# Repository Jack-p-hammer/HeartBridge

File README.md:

# HeartBridge

Software, electronics, mechanical parts and simulation for HeartBridge, an automated CPR machine. The project started as MIT 2.009 Green Team's 2025 class project and has continued since.

## Repository layout

| Folder | Contents |
|---|---|
| [`Raspberry Pi code/`](Raspberry%20Pi%20code/) | The Python controller that runs on the Raspberry Pi: state machine, sensing, motor control (moteus), screen and audio prompts, tests and bench scripts. See its [README](Raspberry%20Pi%20code/README.md) for setup. |
| `hardware/pcb/main-board/` | KiCad project for the main CPR machine board, plus its fab outputs in `production/` |
| `hardware/pcb/mcu-board/` | KiCad project for the MCU board |
| `hardware/pcb/contactor-board/` | KiCad project for the contactor board |
| `hardware/pcb/single-pager-legacy/` | Earlier single-sheet version of main board, kept for reference |
| `hardware/mechanical/` | 3D-print sources (`.step`, `.3mf`) for the current HeartBridge iteration |
| `simulation/` | Simulink model (`Heartbridge.slx`) and supporting MATLAB scripts. `legacy-m4/` holds the force sensor calibration from the class project. |
| `docs/` | Project documentation |

## Getting started

- **Controller code:** follow [`Raspberry Pi code/README.md`](Raspberry%20Pi%20code/README.md).
- **PCBs:** open the `.kicad_pro` file in a board's folder with KiCad. Custom symbol and footprint libraries live inside each board folder and are referenced relative to it.
- **Simulation:** in MATLAB, run `simulinkSetup.m` then open `Heartbridge.slx`.

## History

The repository was reorganized out of its class-project layout (`M3`–`M6`, `CPR Machine`, etc.) in October 2026. Older work is kept in tags rather than folders:

- `pre-restructure`: the last commit before the reorganization
- `archive/final`, `archive/integration`, `archive/zeroing`, `archive/hmi_v2`: class-era branches

To look at one, run `git checkout <tag>`. To keep working from one, create a branch: `git switch -c <name> <tag>`.

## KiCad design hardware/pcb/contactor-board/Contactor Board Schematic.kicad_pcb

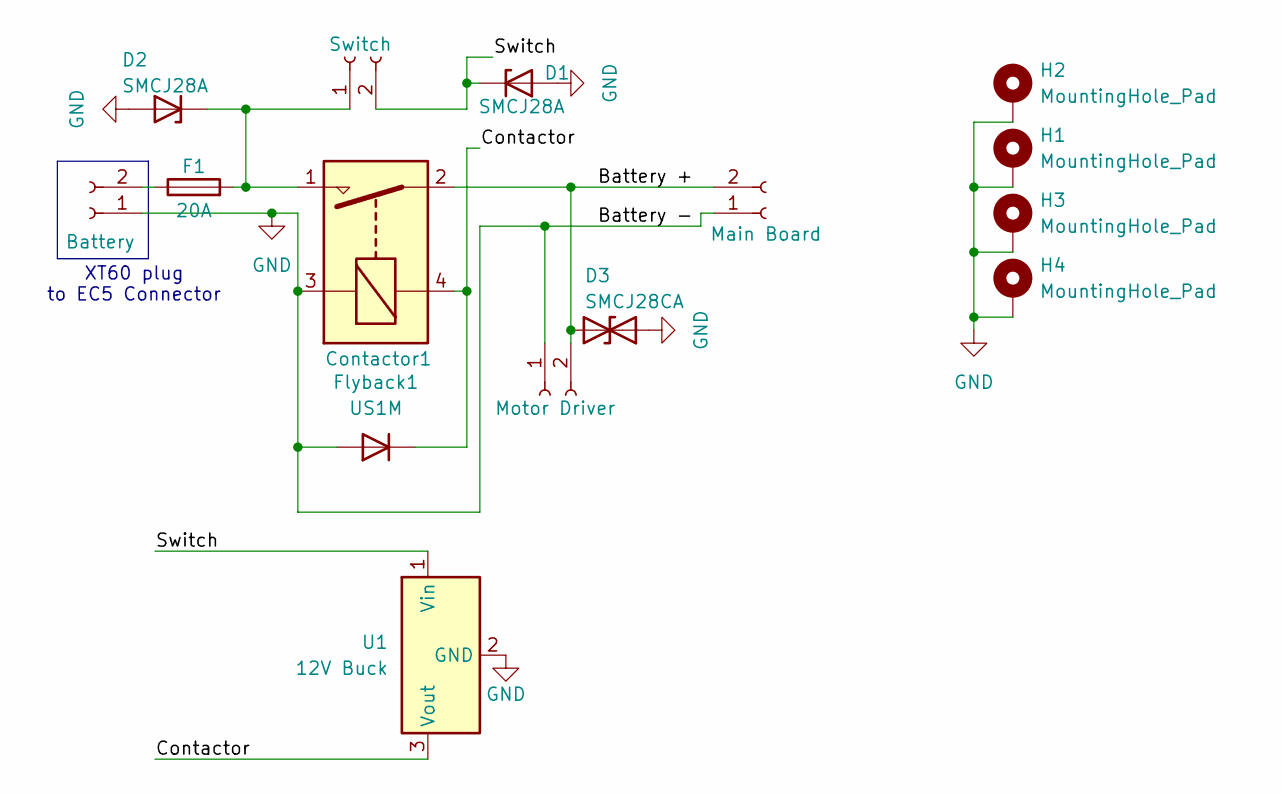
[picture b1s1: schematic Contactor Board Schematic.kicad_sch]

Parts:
Contactor1: AEV20E-BP; AEV20EBP; digikey 2040-AEV20E-BP-ND
D1, D2: SMCJ28A; D_SMC; digikey SMCJ28ALFCT-ND
D3: SMCJ28CA; D_SMC; digikey SMCJ28CALFCT-ND
F1: 20A; Fuse_1206_3216Metric; digikey 5923-0685H9200-01CT-ND
Flyback1: US1M; D_SMA; digikey 4878-US1MCT-ND
H1, H2, H3, H4: MountingHole_Pad; MountingHole_2.7mm_Pad
J_EXT1: Main Board; AMASS_XT30U-M_1x02_P5.0mm_Vertical
J_EXT2: Battery; AMASS_XT60-M_1x02_P7.20mm_Vertical
J_EXT3: Motor Driver; AMASS_XT30U-M_1x02_P5.0mm_Vertical
J_EXT4: Switch; AMASS_XT30U-M_1x02_P5.0mm_Vertical
U1: 12V Buck; Converter_DCDC_TRACO_TSR-1_THT; digikey 1951-2739-ND

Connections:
/Battery +: Contactor1.2, D3.2 (A2), J_EXT1.2, J_EXT3.2
/Contactor: Contactor1.4, Flyback1.1 (K), U1.3 (Vout)
/Switch: D1.1 (K), J_EXT4.2, U1.1 (Vin)
GND: Contactor1.3, D1.2 (A), D2.2 (A), D3.1 (A1), Flyback1.2 (A), H1.1 (1_1), H2.1 (1_1), H3.1 (1_1), H4.1 (1_1), J_EXT1.1, J_EXT2.1, J_EXT3.1, U1.2 (GND)
unnamed: Contactor1.1, D2.1 (K), F1.2, J_EXT4.1
unnamed: F1.1, J_EXT2.2

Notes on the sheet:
XT60 plug to EC5 Connector

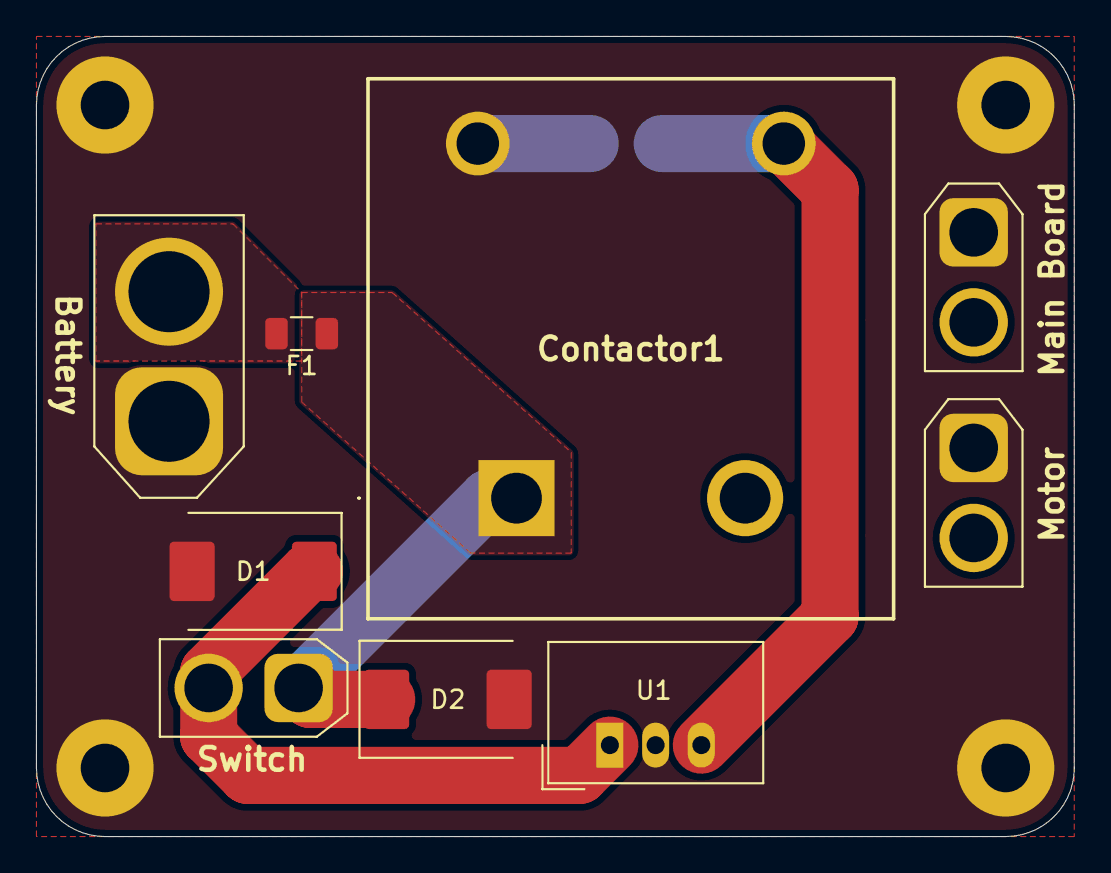
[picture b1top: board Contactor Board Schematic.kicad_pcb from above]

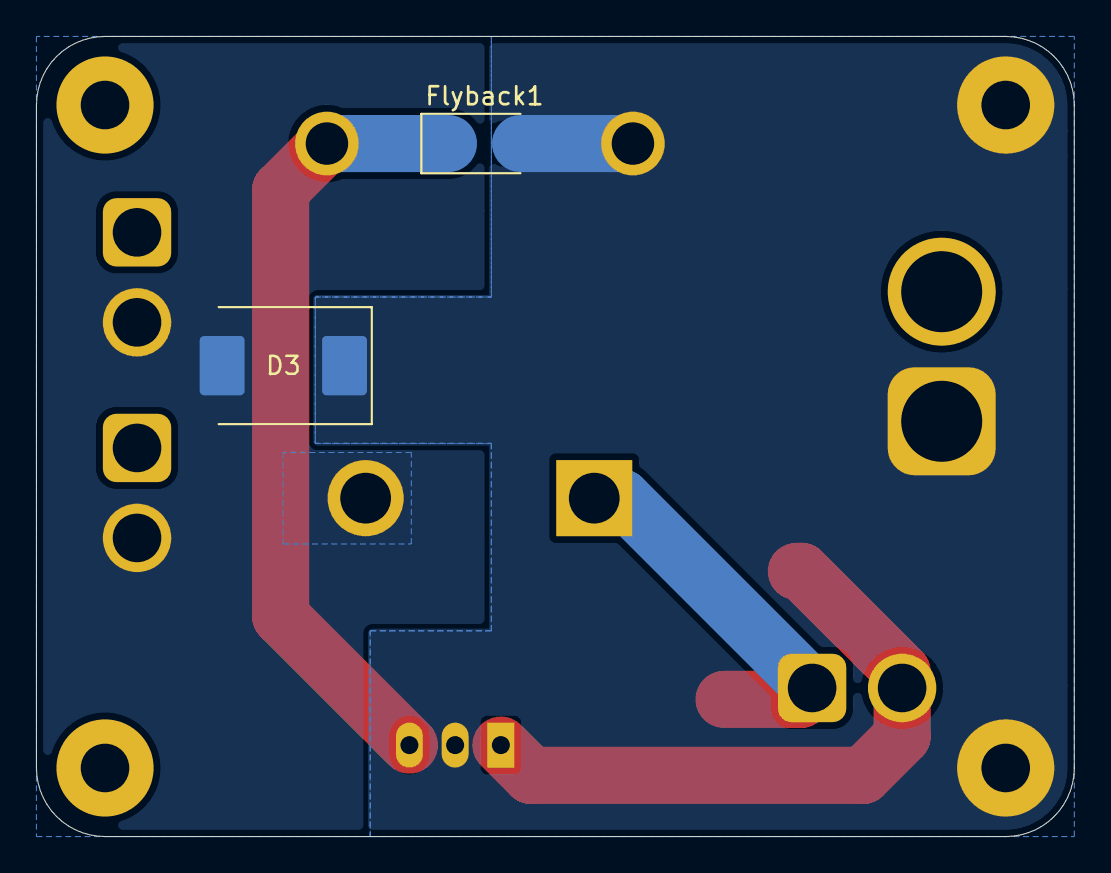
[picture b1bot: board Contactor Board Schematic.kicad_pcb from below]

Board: 2 copper layers, 57.7 x 44.5 mm, 15 parts (2 on the bottom side), 6 nets.

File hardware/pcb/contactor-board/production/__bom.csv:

Designator,Footprint,Quantity,Value,LCSC Part #
CONTACTOR1,AEV20EBP,1,AEV20E-BP,
"D1, D2",D_SMC,2,SMCJ28A,
D3,D_SMC,1,SMCJ28CA,
F1,1206,1,20A,
FLYBACK1,D_SMA,1,US1M,
J_EXT1,AMASS_XT30U-M_1x02_P5.0mm_Vertical,1,Main Board,
J_EXT2,AMASS_XT60-M_1x02_P7.20mm_Vertical,1,Battery,
J_EXT3,AMASS_XT30U-M_1x02_P5.0mm_Vertical,1,Motor Driver,
J_EXT4,AMASS_XT30U-M_1x02_P5.0mm_Vertical,1,Switch,
U1,Converter_DCDC_TRACO_TSR-1_THT,1,12V Buck,

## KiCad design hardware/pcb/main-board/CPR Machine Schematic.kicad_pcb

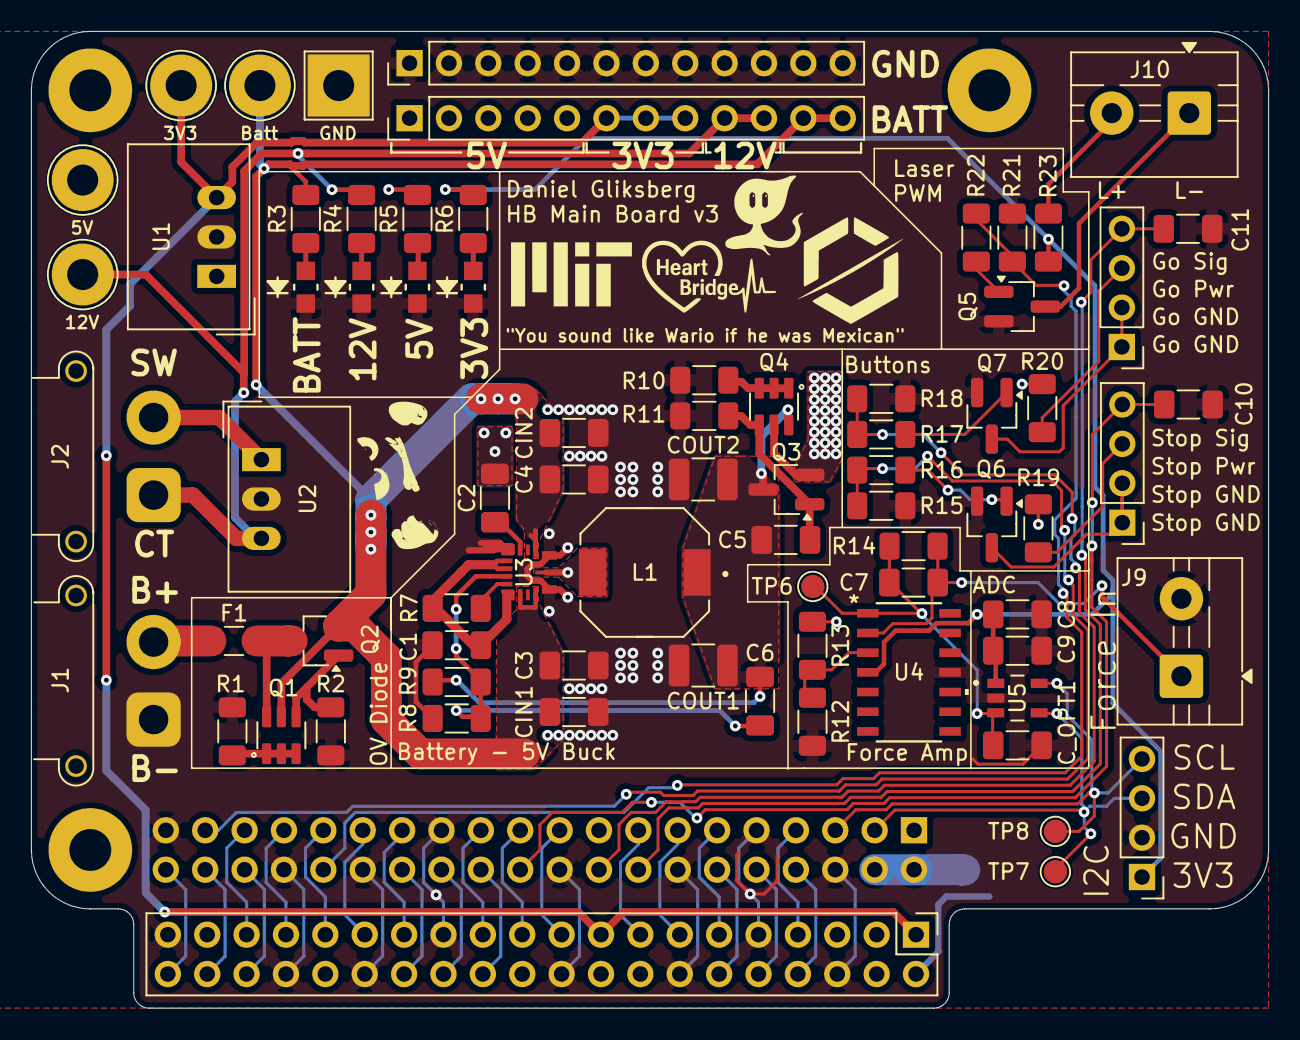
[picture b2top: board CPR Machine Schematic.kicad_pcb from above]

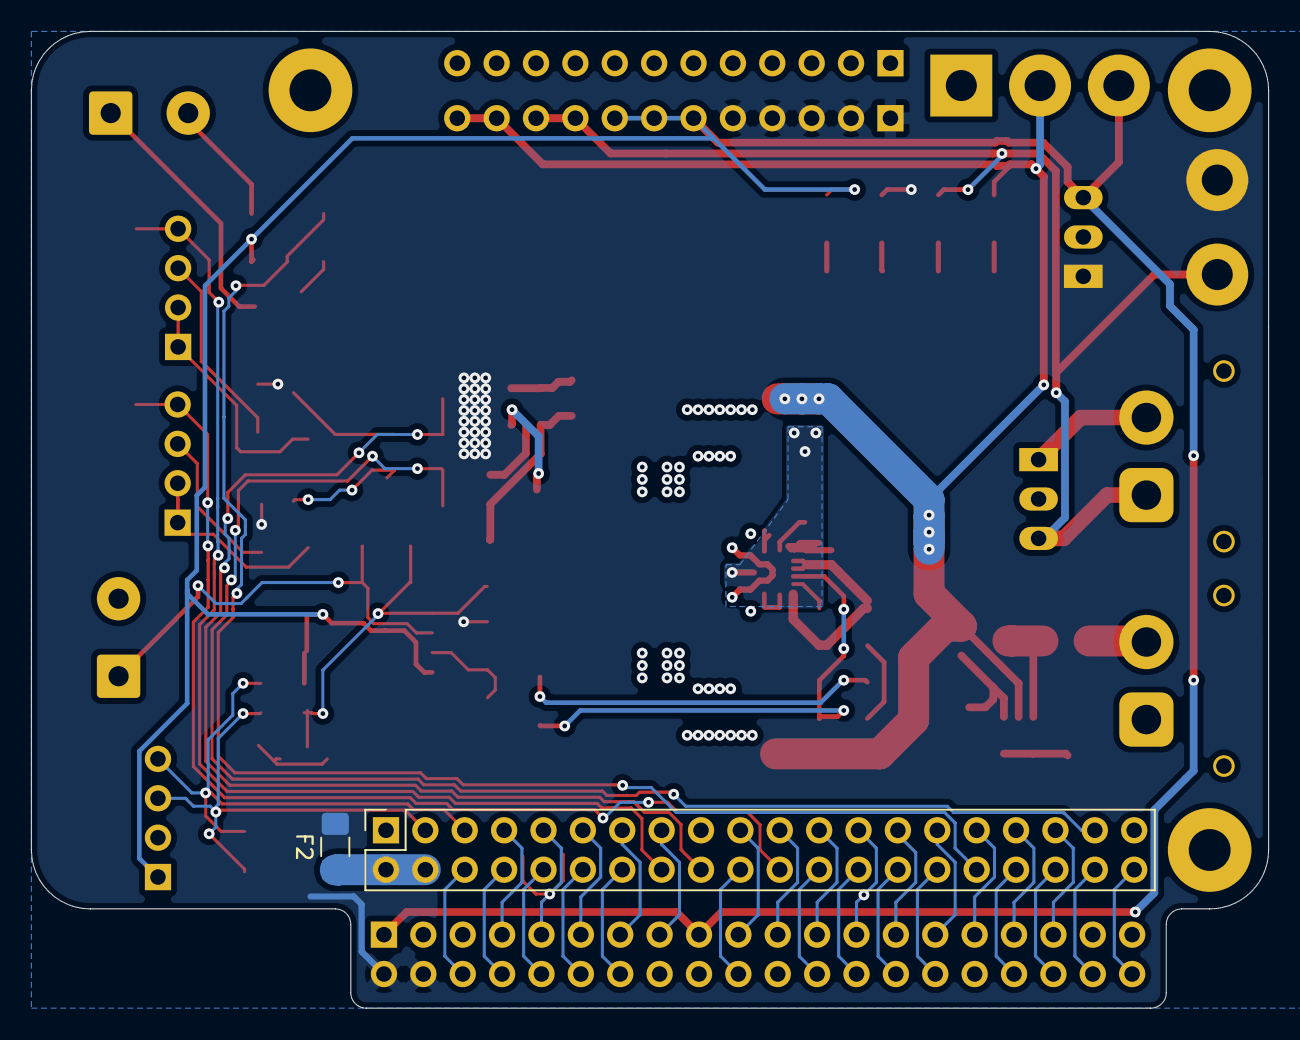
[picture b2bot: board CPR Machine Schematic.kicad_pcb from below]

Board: 2 copper layers, 79.8 x 63.0 mm, 80 parts (2 on the bottom side), 63 nets.

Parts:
C1: 2.2 uF; C_1206_3216Metric_Pad1.33x1.80mm_HandSolder
C2, C3, C4, C9: 0.1 uF; C_1206_3216Metric_Pad1.33x1.80mm_HandSolder
C5: 10 nF; C_1206_3216Metric_Pad1.33x1.80mm_HandSolder
C6, C7: 47 pF; C_1206_3216Metric_Pad1.33x1.80mm_HandSolder
C8: 10 uF; C_1206_3216Metric_Pad1.33x1.80mm_HandSolder
C10, C11: 100 nF; C_1206_3216Metric_Pad1.33x1.80mm_HandSolder
CIN1, CIN2: 2.2 uF; C_1206_3216Metric_Pad1.33x1.80mm_HandSolder
COUT1, COUT2: 23.7 uF; C_1210_3225Metric_Pad1.33x2.70mm_HandSolder
C_OPT1: 47 pF; C_1206_3216Metric_Pad1.33x1.80mm_HandSolder
F1: 4A; Fuse_1206_3216Metric_Pad1.42x1.75mm_HandSolder
F2: 3A; Fuse_1206_3216Metric_Pad1.42x1.75mm_HandSolder
H1, H2, H3: MountingHole; MountingHole_2.7mm_M2.5_Pad
J1: Battery 22.2V IN; AMASS_XT30PW-F_1x02_P2.50mm_Horizontal
J2: Power Switch; AMASS_XT30PW-F_1x02_P2.50mm_Horizontal
J3: GND Spare Headers; PinHeader_1x12_P2.54mm_Vertical
J4: +V Spare Headers; PinHeader_1x12_P2.54mm_Vertical
J5: Conn_02x20_Odd_Even; PinHeader_2x20_P2.54mm_Vertical
J6: I2C Port; PinHeader_1x04_P2.54mm_Vertical
J7: Stop Button Port; PinHeader_1x04_P2.54mm_Vertical
J8: Go Button Port; PinHeader_1x04_P2.54mm_Vertical
J9: Force Sensor; TerminalBlock_MaiXu_MX126-5.0-02P_1x02_P5.00mm
J10: Laser Port; TerminalBlock_MaiXu_MX126-5.0-02P_1x02_P5.00mm
J11: Raspberry_Pi_2_3; PinSocket_2x20_P2.54mm_Vertical
L1: 2.2 uH; IND_1217AS-H-2R2N=P3
LED1, LED2, LED3, LED4: Green; LED_LTST-C170GKT_LTO
Q1, Q4: DMMT5401 PNP; SOT95P285X140-6N
Q2: SSM3J332R; SOT-23_Handsoldering
Q3: DMG2305UX-EV; SOT-23_Handsoldering
Q5, Q6, Q7: T2N7002BK,LM; SOT-23_Handsoldering
R1, R10, R12, R15, R18, R21: 10 kOhm; R_1206_3216Metric_Pad1.30x1.75mm_HandSolder
R2, R11: 47 kOhm; R_1206_3216Metric_Pad1.30x1.75mm_HandSolder
R3: 1.5 kOhm; R_1206_3216Metric_Pad1.30x1.75mm_HandSolder
R4: 665 Ohm; R_1206_3216Metric_Pad1.30x1.75mm_HandSolder
R5: 220 Ohm; R_1206_3216Metric_Pad1.30x1.75mm_HandSolder
R6, R16, R17, R22: 100 Ohm; R_1206_3216Metric_Pad1.30x1.75mm_HandSolder
R7: 20 kOhm; R_1206_3216Metric_Pad1.30x1.75mm_HandSolder
R8: 9.5 kOhm; R_1206_3216Metric_Pad1.30x1.75mm_HandSolder
R9: 49.9 kOhm; R_1206_3216Metric_Pad1.30x1.75mm_HandSolder
R13: 90 kOhm; R_1206_3216Metric_Pad1.30x1.75mm_HandSolder
R14: 80.6 kOhm; R_1206_3216Metric_Pad1.30x1.75mm_HandSolder
R19, R20: 49.9 Ohm; R_1206_3216Metric_Pad1.30x1.75mm_HandSolder
R23: 0 Ohm; R_1206_3216Metric_Pad1.30x1.75mm_HandSolder
TP1: 12 V; TestPoint_THTPad_D4.0mm_Drill2.0mm
TP2: 5 V; TestPoint_THTPad_D4.0mm_Drill2.0mm
TP3: 3V3; TestPoint_THTPad_D4.0mm_Drill2.0mm
TP4: Battery; TestPoint_THTPad_D4.0mm_Drill2.0mm
TP5: GND; TestPoint_THTPad_4.0x4.0mm_Drill2.0mm
TP6: Amp Out; TestPoint_Pad_D1.5mm
TP7: SDA; TestPoint_Pad_D1.5mm
TP8: SCL; TestPoint_Pad_D1.5mm
U1: 3.3V Buck; Converter_DCDC_TRACO_TSR-1_THT
U2: 12V Buck; Converter_DCDC_TRACO_TSR-1_THT
U3: MAX42403AFLB+; 21-100701_90-100241_ADI
U4: MCP6004; SOIC14_SL_MCH
U5: MCP3021A5T-E_OT; IC_MCP3021A0T-E_OT

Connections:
+3.3V: C8.2, C9.2, J4.6, J4.7, J4.8, J5.1, J5.17, J6.1, R6.2, R23.1, TP3.1, U1.3 (Vout), U4.4 (V+), U5.1 (VDD)
+5V: F2.1, J4.1, J4.2, J4.3, J4.4, J4.5, J5.2, J5.4, Q3.2, Q4.5, R5.2, R13.1, R19.2, R20.2, TP2.1, U1.1 (Vin)
+12V: J2.1, J4.9, J4.10, R4.2, TP1.1, U2.3 (Vout)
+22.2V: C3.2, C4.2, CIN1.2, CIN2.2, J4.11, J4.12, Q1.5, Q2.2, R3.2, TP4.1, U3.1 (EN), U3.3 (SUP), U3.7 (SUP)
/HMI_Raspi/Go Button: C11.2, J8.4, J11.16 (GPIO23)
/HMI_Raspi/Go Button Ground: J8.1, J8.2, Q7.3 (D)
/HMI_Raspi/Go LED Power: J8.3, R20.1
/HMI_Raspi/Go_Enable: J11.18 (GPIO24), R17.1, R18.1
/HMI_Raspi/Laser_PWM: J11.32 (PWM0/GPIO12), R21.1, R22.1
/HMI_Raspi/Stop Button: C10.2, J7.4, J11.22 (GPIO25)
/HMI_Raspi/Stop Button Ground: J7.1, J7.2, Q6.3 (D)
/HMI_Raspi/Stop LED Power: J7.3, R19.1
/HMI_Raspi/Stop_Enable: J11.37 (GPIO26), R15.1, R16.1
/Power/BST: C2.2, U3.9 (BST)
/Power/Battery +: F1.1, J1.2
/Power/From Switch: J2.2, U2.1 (Vin)
/Power/LX: C2.1, L1.2, U3.5 (LX)
/Power/Reg OUT: C5.2, C6.2, COUT1.1, COUT2.1, L1.1, Q3.3, Q4.6, R9.1
/Raspi/GPIO0: J5.27, J11.27 (ID_SD/GPIO0)
/Raspi/GPIO1: J5.28, J11.28 (ID_SC/GPIO1)
/Raspi/GPIO4: J5.7, J11.7 (GCLK0/GPIO4)
/Raspi/GPIO5: J5.29, J11.29 (GCLK1/GPIO5)
/Raspi/GPIO6: J5.31, J11.31 (GCLK2/GPIO6)
/Raspi/GPIO7: J5.26, J11.26 (~CE1/GPIO7)
/Raspi/GPIO8: J5.24, J11.24 (~CE0/GPIO8)
/Raspi/GPIO9: J5.21, J11.21 (MISO0/GPIO9)
/Raspi/GPIO10: J5.19, J11.19 (MOSI0/GPIO10)
/Raspi/GPIO11: J5.23, J11.23 (SCLK0/GPIO11)
/Raspi/GPIO13: J5.33, J11.33 (PWM1/GPIO13)
/Raspi/GPIO14: J5.8, J11.8 (GPIO14/TXD)
/Raspi/GPIO15: J5.10, J11.10 (GPIO15/RXD)
/Raspi/GPIO16: J5.36, J11.36 (GPIO16)
/Raspi/GPIO17: J5.11, J11.11 (GPIO17)
/Raspi/GPIO18: J5.12, J11.12 (GPIO18/PWM0)
/Raspi/GPIO19: J5.35, J11.35 (GPIO19/MISO1)
/Raspi/GPIO20: J5.38, J11.38 (GPIO20/MOSI1)
/Raspi/GPIO21: J5.40, J11.40 (GPIO21/SCLK1)
/Raspi/GPIO22: J5.15, J11.15 (GPIO22)
/Raspi/GPIO27: J5.13, J11.13 (GPIO27)
/Raspi/I2C_SCL: J6.4, J11.5 (SCL/GPIO3), TP8.1, U5.5 (SCL)
/Raspi/I2C_SDA: J6.3, J11.3 (SDA/GPIO2), TP7.1, U5.4 (SDA)
/Sensing/Vref: R12.1, R13.2, U4.3 (+)
GND: C1.1, C3.1, C4.1, C8.1, C9.1, C10.1, C11.1, CIN1.1, CIN2.1, COUT1.2, COUT2.2, C_OPT1.1, J1.1, J3.1, J3.2, J3.3, J3.4, J3.5, J3.6, J3.7, J3.8, J3.9, J3.10, J3.11, J3.12, J5.6, J5.9, J5.14, J5.20, J5.25, J5.30, J5.34, J5.39, J6.2, J9.2, J11.6 (GND), J11.9 (GND), J11.14 (GND), J11.20 (GND), J11.25 (GND), J11.30 (GND), J11.34 (GND), J11.39 (GND), LED1.1, LED2.1, LED3.1, LED4.1, Q5.2 (S), Q6.2 (S), Q7.2 (S), R1.2, R2.2, R8.2, R10.2, R11.2, R12.2, R15.2, R18.2, R21.2, TP5.1, U1.2 (GND), U2.2 (GND), U3.4 (PGND), U3.6 (PGND), U3.10 (GND), U4.11 (V-), U5.2 (VSS)
unnamed: C5.1, Q3.1, Q4.4, R11.1
unnamed: F1.2, Q1.6, Q2.3
unnamed: F2.2, J11.2 (5V), J11.4 (5V)
unnamed: C7.1, J9.1, R14.2, U4.2 (-)
unnamed: J10.1, Q5.3 (D)
unnamed: J10.2, R23.2
unnamed: LED1.2, R4.1
unnamed: LED2.2, R3.1
unnamed: LED3.2, R5.1
unnamed: LED4.2, R6.1
unnamed: Q1.1, Q1.2, Q1.3, R1.1
unnamed: Q1.4, Q2.1, R2.1
unnamed: Q4.1, Q4.2, Q4.3, R10.1
unnamed: Q5.1 (G), R22.2
unnamed: Q6.1 (G), R16.2
unnamed: Q7.1 (G), R17.2
unnamed: C1.2, R7.2, U3.11 (BIAS), U3.12 (SPS), U3.15 (SYNC)
unnamed: C6.1, R8.1, R9.2, U3.13 (FB)
unnamed: R7.1, U3.14 (PGOOD)
unnamed: C7.2, C_OPT1.2, R14.1, TP6.1, U4.1, U5.3 (AIN)

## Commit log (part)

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2026-03-29 Battery Tracking
2026-03-29 Audio buzzing fixed
2026-04-28 Final PCB
2026-05-07 PCB V1 Final
2026-05-10 Code V3 Start
2026-05-11 Barebones state machine
2026-05-19 test for pulling on pi
2026-05-19 Uploaded images and audio files
2026-05-19 Set up package management
2026-05-19 Package Management part 2
2026-05-19 attempting to sensor
2026-05-19 AV Initialization
2026-05-19 Image Display maybe?
2026-05-19 Some file structure refactoring
2026-06-02 Start of Board V2
2026-06-02 Fixed edge cuts
2026-06-07 Board V2
2026-06-12 Board V2 Final
2026-06-18 Printing Files
2026-06-18 middle printing file
2026-06-22 more printing files
2026-06-26 Final PCB V2
2026-06-28 Python code started
    run:
    pip install -r requirements.txt
    in the project directory on your device to download required packages
2026-06-28 File structure, claude-ed code port
2026-06-28 asset path comment
2026-06-28 Make device log its own directory
2026-06-28 One comment
2026-06-28 Pre-created log file
2026-06-28 Log file directory resolve(), state machine changes
2026-06-28 File path resolve()s, typecasting
2026-06-29 moteus module
2026-06-29 autopep8 formatting
2026-06-29 gitignore, readme, and updated module requirements
2026-06-29 Testing framework
2026-06-29 logs now timestamped
2026-06-29 comments about logging vs printing
2026-06-29 Voltage readout, MUX, Debouncing Caps
2026-06-30 MUX, Debounce Caps, I2C Testpoints
2026-06-30 slight pcb changes
2026-06-30 I2C Scanner script
2026-06-30 Change placeholder pins to real pins
2026-06-30 Added reading functionality for IMU and ToF
